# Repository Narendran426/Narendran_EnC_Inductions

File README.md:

# Narendran_EnC_Inductions
Kratos EnC Induction stuff here

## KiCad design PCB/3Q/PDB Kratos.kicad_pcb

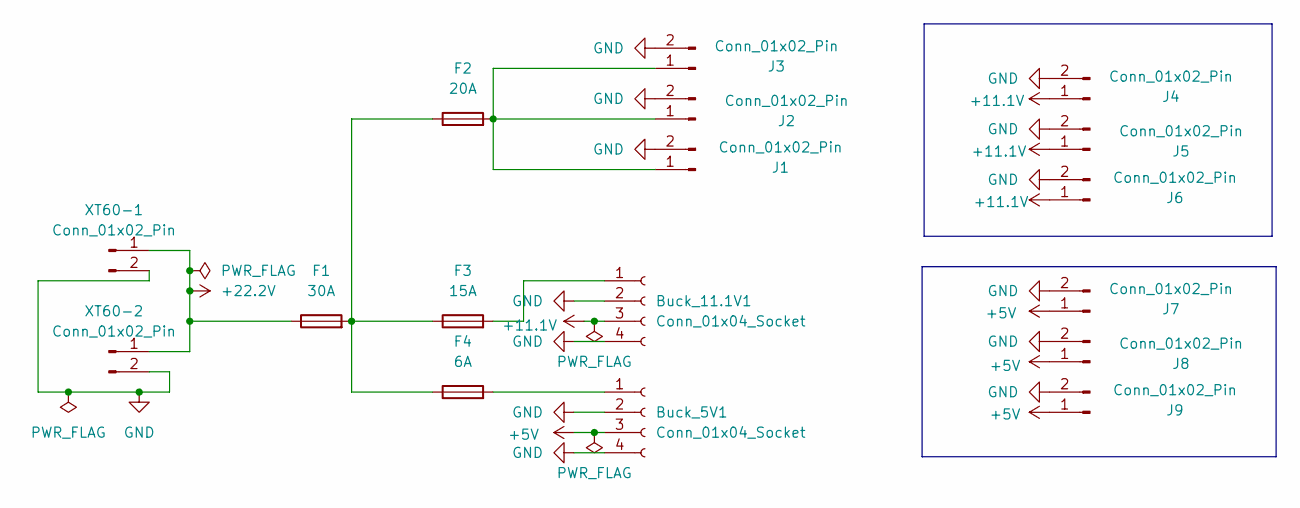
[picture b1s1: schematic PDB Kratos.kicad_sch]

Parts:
Buck_5V1: Conn_01x04_Socket; 5A Buck
Buck_11.1V1: Conn_01x04_Socket; 20A Buck
F1: 30A; Fuse_Blade_ATO_directSolder
F2: 20A; Fuse_Blade_ATO_directSolder
F3: 15A; Fuse_Blade_ATO_directSolder
F4: 6A; Fuse_Blade_ATO_directSolder
J1, J2, J3: Conn_01x02_Pin; AMASS_XT60-M_1x02_P7.20mm_Vertical
J4, J5, J6, J7, J8, J9: Conn_01x02_Pin; AMASS_XT30U-M_1x02_P5.0mm_Vertical
XT60-1, XT60-2: Conn_01x02_Pin; AMASS_XT60-M_1x02_P7.20mm_Vertical

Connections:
+5V: Buck_5V1.3, J7.1, J8.1, J9.1
+11.1V: Buck_11.1V1.3, J4.1, J5.1, J6.1
+22.2V: F1.1, XT60-1.1, XT60-2.1
GND: Buck_5V1.2, Buck_5V1.4, Buck_11.1V1.2, Buck_11.1V1.4, J1.2, J2.2, J3.2, J4.2, J5.2, J6.2, J7.2, J8.2, J9.2, XT60-1.2, XT60-2.2
unnamed: Buck_5V1.1, F4.2
unnamed: Buck_11.1V1.1, F3.2
unnamed: F1.2, F2.1, F3.1, F4.1
unnamed: F2.2, J1.1, J2.1, J3.1

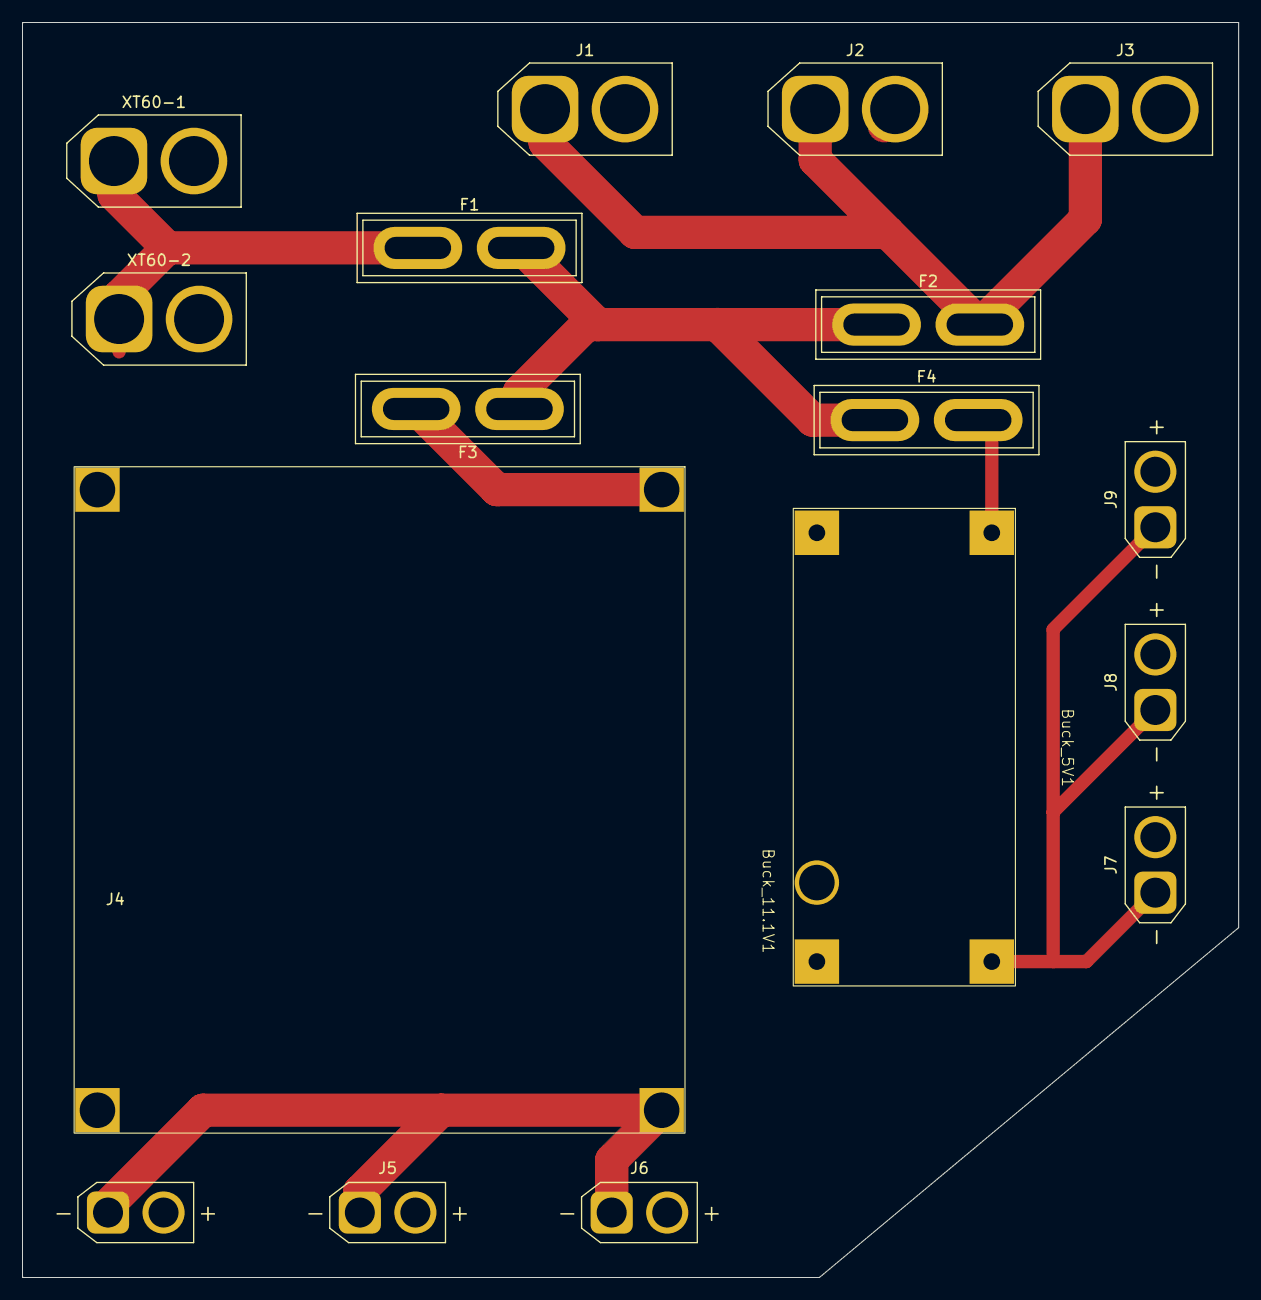
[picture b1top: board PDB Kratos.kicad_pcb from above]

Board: 2 copper layers, 109.5 x 113.0 mm, 17 parts (0 on the bottom side), 8 nets.

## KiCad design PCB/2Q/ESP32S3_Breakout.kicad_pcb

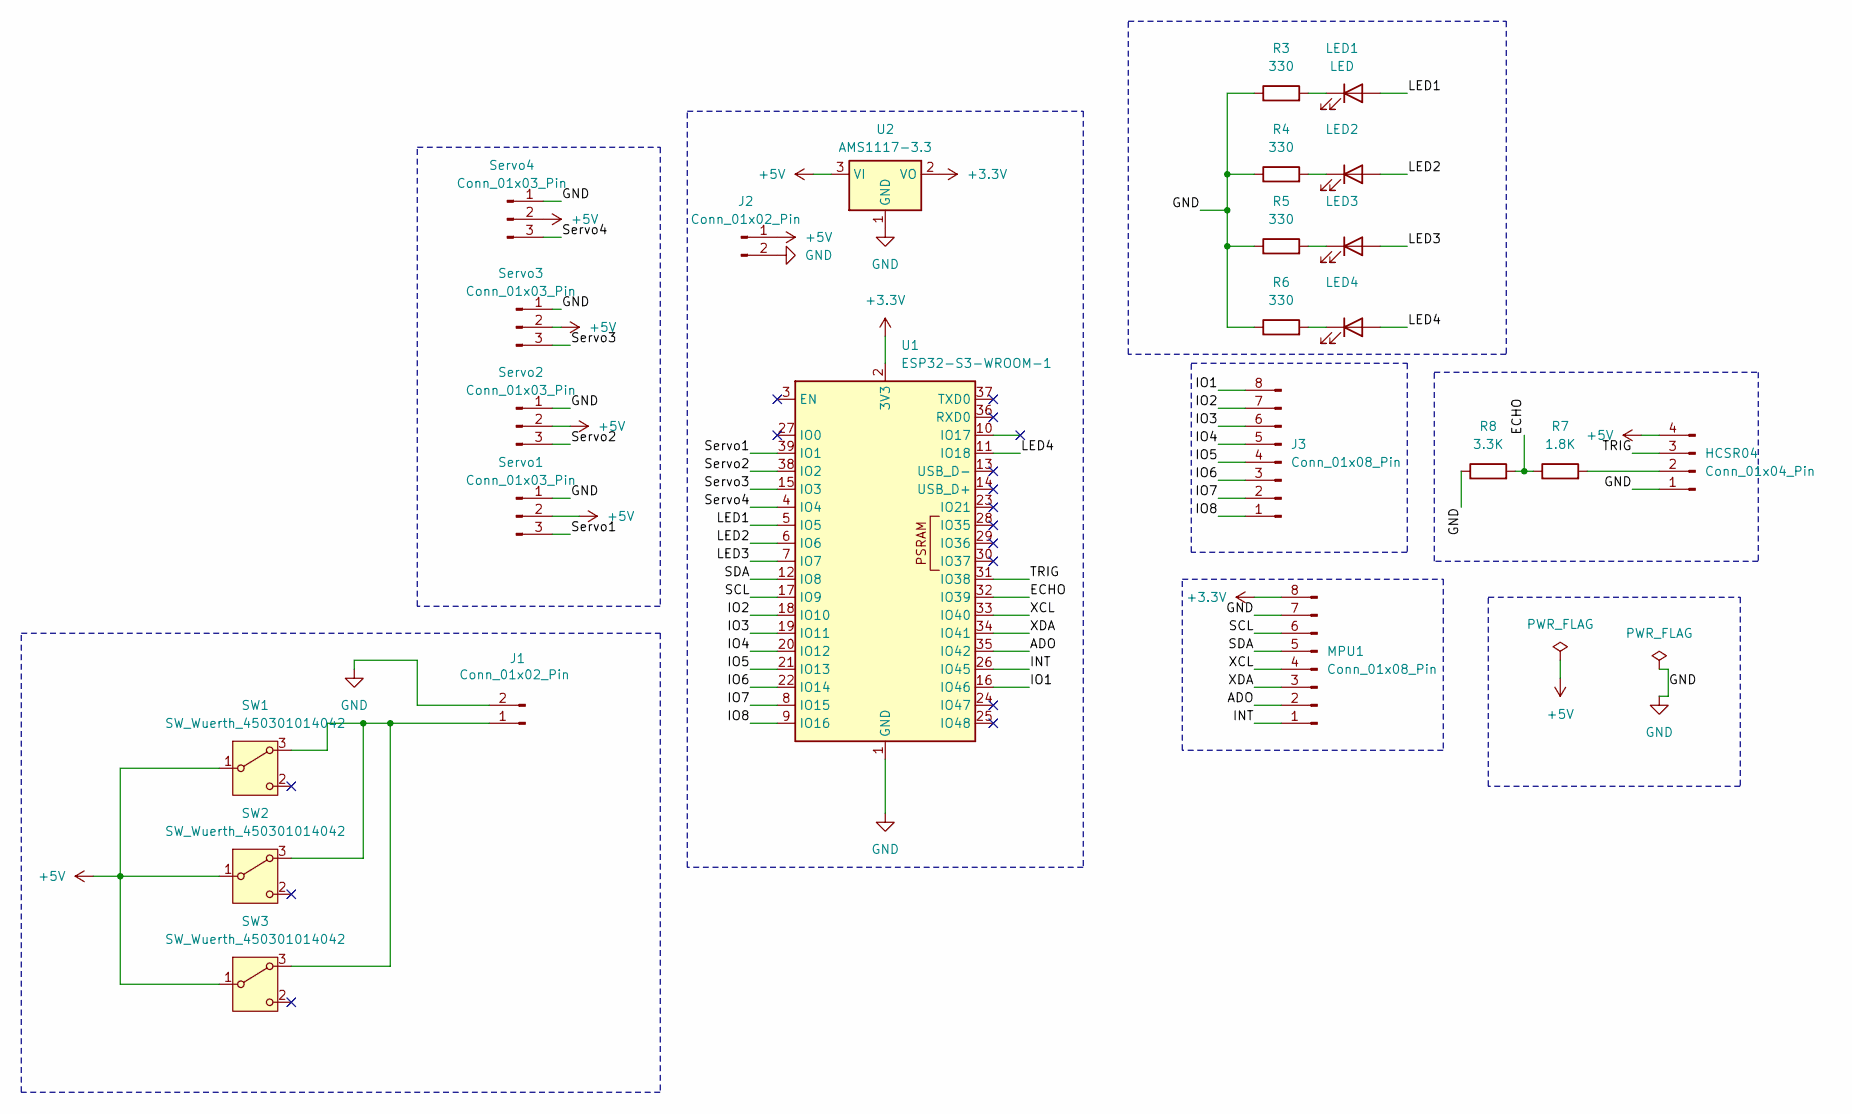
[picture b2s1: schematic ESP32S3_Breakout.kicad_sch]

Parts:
HCSR04: Conn_01x04_Pin; NS-Tech_Grove_1x04_P2mm_Vertical
J1: Conn_01x02_Pin; Hirose_DF13-02P-1.25DSA_1x02_P1.25mm_Vertical
J2: Conn_01x02_Pin; AMASS_XT30U-F_1x02_P5.0mm_Vertical
J3: Conn_01x08_Pin; Hirose_DF13-08P-1.25DSA_1x08_P1.25mm_Vertical
LED1, LED2, LED3, LED4: LED; LED_0201_0603Metric
MPU1: Conn_01x08_Pin; Hirose_DF13-08P-1.25DSA_1x08_P1.25mm_Vertical
R3, R4, R5, R6: 330; R_0201_0603Metric
R7: 1.8K; R_0201_0603Metric
R8: 3.3K; R_0201_0603Metric
SW1, SW2, SW3: SW_Wuerth_450301014042; SW_Slide-03_Wuerth-WS-SLTV_10x2.5x6.4_P2.54mm
Servo1, Servo2, Servo3, Servo4: Conn_01x03_Pin; JST_EH_B3B-EH-A_1x03_P2.50mm_Vertical
U1: ESP32-S3-WROOM-1
U2: AMS1117-3.3; SOT-223-3_TabPin2

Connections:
+3.3V: MPU1.8, U1.2 (3V3), U2.2 (VO)
+5V: HCSR04.4, J2.1, SW1.1 (B), SW2.1 (B), SW3.1 (B), Servo1.2, Servo2.2, Servo3.2, Servo4.2, U2.3 (VI)
/ADO: MPU1.2, U1.35 (IO42)
/ECHO: R7.1, R8.2, U1.32 (IO39)
/INT: MPU1.1, U1.26 (IO45)
/IO1: J3.8, U1.16 (IO46)
/IO2: J3.7, U1.18 (IO10)
/IO3: J3.6, U1.19 (IO11)
/IO4: J3.5, U1.20 (IO12)
/IO5: J3.4, U1.21 (IO13)
/IO6: J3.3, U1.22 (IO14)
/IO7: J3.2, U1.8 (IO15)
/IO8: J3.1, U1.9 (IO16)
/LED1: LED1.2 (A), U1.5 (IO5)
/LED2: LED2.2 (A), U1.6 (IO6)
/LED3: LED3.2 (A), U1.7 (IO7)
/LED4: LED4.2 (A), U1.11 (IO18)
/SCL: MPU1.6, U1.17 (IO9)
/SDA: MPU1.5, U1.12 (IO8)
/Servo1: Servo1.3, U1.39 (IO1)
/Servo2: Servo2.3, U1.38 (IO2)
/Servo3: Servo3.3, U1.15 (IO3)
/Servo4: Servo4.3, U1.4 (IO4)
/TRIG: HCSR04.3, U1.31 (IO38)
/XCL: MPU1.4, U1.33 (IO40)
/XDA: MPU1.3, U1.34 (IO41)
GND: HCSR04.1, J1.2, J2.2, MPU1.7, R3.1, R4.1, R5.1, R6.1, R8.1, Servo1.1, Servo2.1, Servo3.1, Servo4.1, U1.1 (GND), U1.40 (GND), U1.41 (GND), U2.1 (GND)
unnamed: HCSR04.2, R7.2
unnamed: J1.1, SW1.3 (A), SW2.3 (A), SW3.3 (A)
unnamed: LED1.1 (K), R3.2
unnamed: LED2.1 (K), R4.2
unnamed: LED3.1 (K), R5.2
unnamed: LED4.1 (K), R6.2

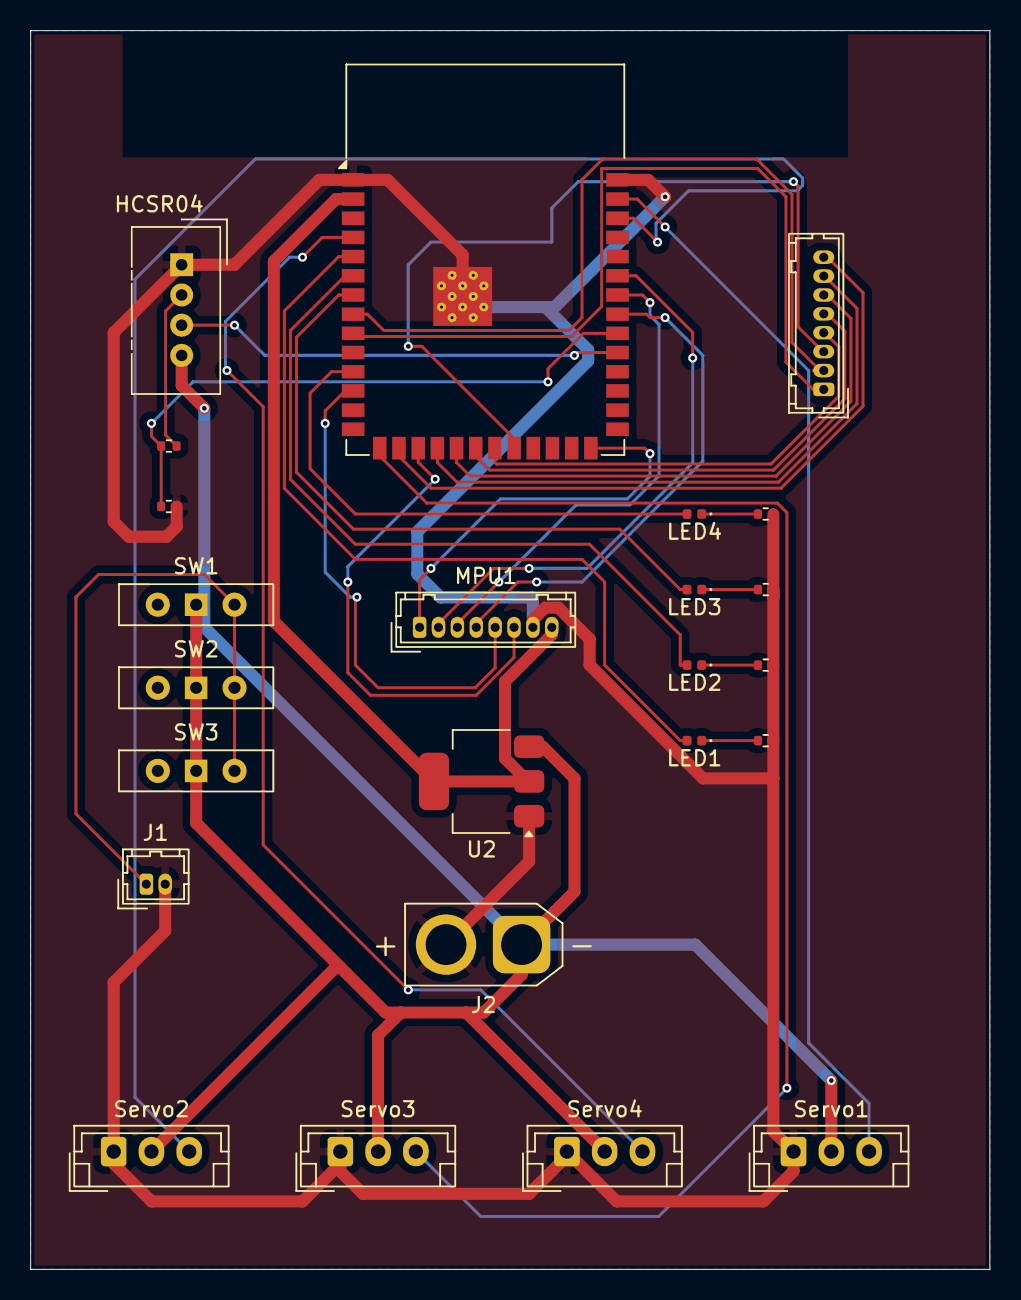
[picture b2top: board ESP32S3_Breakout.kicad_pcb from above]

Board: 2 copper layers, 63.5 x 82.0 mm, 24 parts (0 on the bottom side), 33 nets.

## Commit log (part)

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2026-06-29 Add initial PCB header with placeholder text
2026-06-29 Add 2Q file with content '2nd qs'
2026-06-29 Create temp
2026-06-29 Create Under construction
